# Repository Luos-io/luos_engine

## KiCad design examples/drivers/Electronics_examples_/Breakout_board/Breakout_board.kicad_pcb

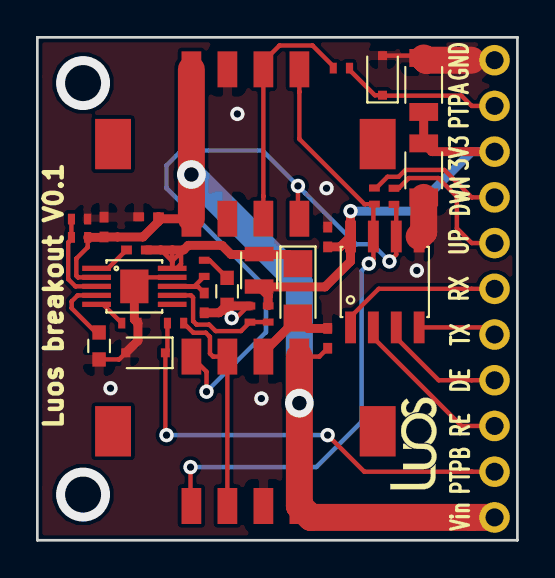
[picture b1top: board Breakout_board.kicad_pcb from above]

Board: 2 copper layers, 26.7 x 27.9 mm, 29 parts (0 on the bottom side), 23 nets.

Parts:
C1, C2, C3: 1µF; C_0402_NoSilk
C4: 27pF; C_0402_NoSilk
C5: 470pF; C_0603
C6: 6.8nF; C_0603
C7, C8: 100nF; C_0402_NoSilk
C9, C10: 47µF; C_1206
D2, D3: D_Zener; D_SOD-323F
D4: SS14FL; SOD-123F
J1, J2: DF11-8DP-2DS(24); DF11C-8DP-2V(57)
J3: Header11Contacts; 826926-11
L1: 4,7µH; L_0806
R1, R2: 100; R_0402_NoSilk
R3: 105K; R_0402_NoSilk
R4: 68.1K; R_0402_NoSilk
R5: 150K; R_0402_NoSilk
R6, R7, R10: 10K; R_0402_NoSilk
R8: 174K; R_0402_NoSilk
R9: 31.6K; R_0402_NoSilk
U1: ST3485ECDR; SO8
U2: TPS5401; S-PDSO-G10

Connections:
+3V3: C7.1, C9.2, C10.2, J3.9, L1.2, R9.1, U1.8
/A_RS_485_N: J1.5, J2.5, R7.1, U1.6
/B_RS_485_P: J1.4, J2.4, R6.2, U1.7
/DE: J3.4, U1.3
/PTPA: D3.1, J3.10, R2.1
/PTPA_PRO: J2.3, J2.6, R2.2
/PTPB: D2.1, J3.2, R1.1
/PTPB_PRO: J1.3, J1.6, R1.2
/RE: J3.3, U1.2
/RS485_LVL_DOWN: J3.8, R6.1
/RS485_LVL_UP: J3.7, R7.2
/RxD: J3.6, U1.1
/TxD: J3.5, U1.4
/Vin: C1.1, C2.1, C3.1, J1.1, J1.8, J2.1, J2.8, J3.1, R3.1, U2.2
GND: C1.2, C2.2, C3.2, C4.2, C5.2, C6.2, C7.2, C9.1, C10.1, D2.2, D3.2, D4.2, J1.2, J1.7, J2.2, J2.7, J3.11, R4.2, R8.2, R10.2, U1.5, U2.9, U2.11
unnamed: C4.1, R5.1, U2.8
unnamed: C5.1, R5.2
unnamed: C6.1, U2.4
unnamed: C8.1, D4.1, L1.1, U2.10
unnamed: C8.2, U2.1
unnamed: R3.2, R4.1, U2.3
unnamed: R8.1, U2.5
unnamed: R9.2, R10.1, U2.7

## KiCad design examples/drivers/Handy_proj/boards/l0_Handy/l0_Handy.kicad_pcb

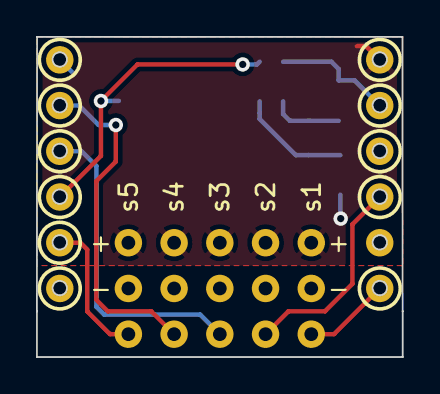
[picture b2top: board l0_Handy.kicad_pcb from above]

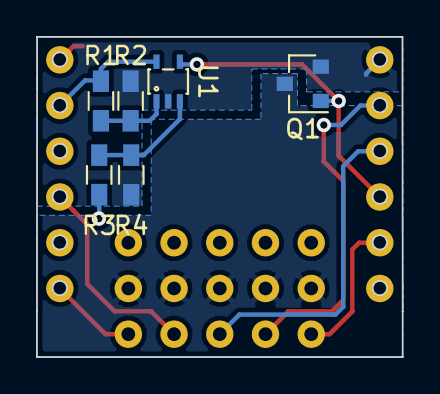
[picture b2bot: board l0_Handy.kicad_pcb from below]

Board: 2 copper layers, 20.3 x 17.8 mm, 12 parts (6 on the bottom side), 12 nets.

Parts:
J1: l0_Shield_Socket; l0_DC_Shield_Socket
Q1: Q_NMOS_GSD; SOT-23
R1: 33k; R_0603_HandSoldering
R2, R4: 10k; R_0603_HandSoldering
R3: 75k; R_0603_HandSoldering
U1: LMV301; SC-70-5
s1, s2, s3, s4, s5: Conn_01x03; servo_header

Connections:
+3V3: J1.5, R1.1, U1.5
/TIM2_CH1: J1.1, s1.1
/TIM2_CH2: J1.3, s2.1
/TIM2_CH3: J1.9, s3.1
/TIM2_CH4: J1.8, s4.1
/TIM3_CH3: J1.11, s5.1
/V_max: J1.10, Q1.1, U1.4
/V_robus_img: R3.2, R4.1, U1.3
GND: J1.7, Q1.2, R2.2, R4.2, U1.2
GNDREF: Q1.3, s1.2, s2.2, s3.2, s4.2, s5.2
unnamed: R1.2, R2.1, U1.1
VCC: J1.6, R3.1, s1.3, s2.3, s3.3, s4.3, s5.3

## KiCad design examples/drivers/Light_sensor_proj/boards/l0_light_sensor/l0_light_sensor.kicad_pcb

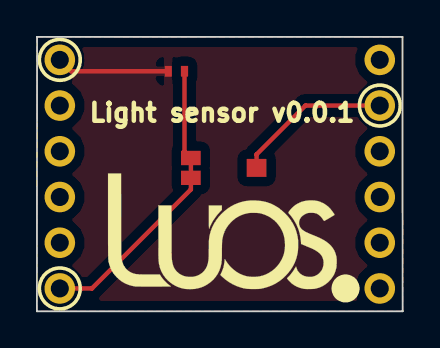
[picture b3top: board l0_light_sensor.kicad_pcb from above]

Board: 2 copper layers, 20.3 x 15.2 mm, 3 parts (0 on the bottom side), 3 nets.

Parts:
J1: l0_Socket; l0_Shield_Socket
Q1: Q_Photo_NPN; TEMT6000
R1: 1K; R_0402_NoSilk

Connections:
GND: J1.7, R1.2
unnamed: J1.5, Q1.1
unnamed: J1.12, Q1.2, R1.1

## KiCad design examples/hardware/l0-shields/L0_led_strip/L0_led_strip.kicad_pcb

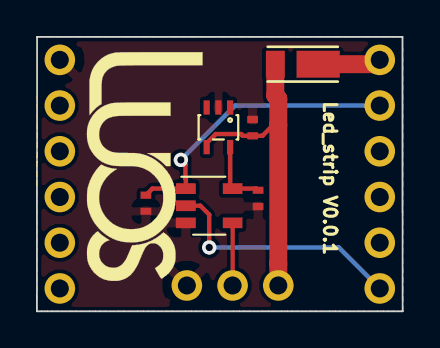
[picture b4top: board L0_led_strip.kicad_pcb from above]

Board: 2 copper layers, 20.3 x 15.2 mm, 8 parts (0 on the bottom side), 7 nets.

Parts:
C1, C3: 100nF; R_0402_NoSilk
C2: 100nf; R_0402_NoSilk
D1: DFLS230L-7; PowerDI-123
J1: l0_Socket; l0_Shield_Socket
J2: Header3Contacts; 826926-3
U1: TPS71550DCKR; SC-70-5
U2: SN74LVC1G126DBVT; SOT-23-5

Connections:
+3V3: C3.1, J1.5, U2.1
+5V: C2.1, U1.5, U2.5
/TX: J1.1, U2.2
/TX_5V: J2.2, U2.4
GND: C1.2, C2.2, C3.2, J1.7, J2.1, U1.2, U2.3
unnamed: D1.1, J1.6
VBUS: C1.1, D1.2, J2.3, U1.4

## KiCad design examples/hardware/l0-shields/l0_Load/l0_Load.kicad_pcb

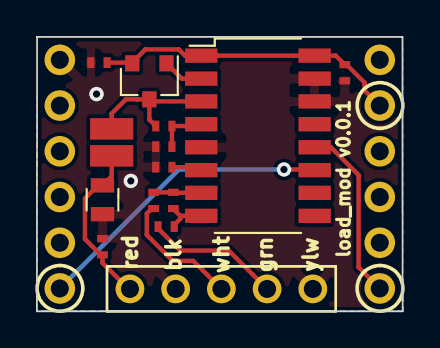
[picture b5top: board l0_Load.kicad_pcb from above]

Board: 2 copper layers, 20.3 x 15.2 mm, 15 parts (0 on the bottom side), 13 nets.

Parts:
C1, C3, C4, C5, C6: 0.1uf; R_0402_NoSilk
C2: 10uf; R_0805
J1: Header5Contacts; 826926-5
J2: l0_Socket; l0_Shield_Socket
L1: 3.3uh; 1008
Q1: Q_NPN_BEC; SOT-23
R1: 20K; R_0402_NoSilk
R2: 8.2K; R_0402_NoSilk
R3, R4: 100; R_0402_NoSilk
U1: HX711; SOP-16_4.4x10.4mm_Pitch1.27mm

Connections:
+3V3: C5.1, C6.1, J2.5, Q1.2, U1.1, U1.16
/A+: J1.4, R4.1
/A-: J1.3, R3.1
/DAT: J2.1, U1.12
/SCK: J2.12, U1.11
GND: C1.2, C2.2, C3.1, C5.2, C6.2, J1.2, J1.5, J2.7, R2.2, U1.5, U1.14, U1.15
unnamed: C1.1, C2.1, J1.1, L1.1
unnamed: C3.2, U1.6
unnamed: C4.1, R3.2, U1.7
unnamed: C4.2, R4.2, U1.8
unnamed: L1.2, Q1.3, R1.1, U1.3
unnamed: Q1.1, U1.2
unnamed: R1.2, R2.1, U1.4
